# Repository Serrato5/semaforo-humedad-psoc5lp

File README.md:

# Semáforo de humedad del suelo para PSoC 5LP

Tarjeta de expansión para la **PSoC 5LP (CY8CKIT-059)** que clasifica la humedad del suelo en **seco, semihúmedo o húmedo** con un semáforo de LED. La decisión es **100 % analógica**: un seguidor de voltaje, dos comparadores y una compuerta NOR internos de la PSoC comparan la señal de un sensor capacitivo con dos umbrales que se ajustan con trimmers. La CPU solo arranca los bloques y reporta el estado por USB.

Proyecto del curso **Electrónica Análoga 3**, Universidad Surcolombiana (Neiva), 2026-B. Docente: Ing. Julián Adolfo Ramírez Gutiérrez.

**[Bitácora del equipo (PDF)](documentos/Bitacora_del_equipo_Grupo4.pdf)** · **[Guía de estudio (PDF)](documentos/Guia_de_estudio_del_proyecto.pdf)** · **[Bitácora del proyecto](https://serrato5.github.io/semaforo-humedad-psoc5lp/bitacora.html)**: el recorrido completo, con los errores y las decisiones · **[Portafolio de Sebastián](https://serrato5.github.io/semaforo-humedad-psoc5lp/)** · **[Video del funcionamiento](https://youtu.be/htcd85bEVA8)**

## Equipo

| Integrante |
|---|
| Sebastián Serrato Ramírez · [LinkedIn](https://www.linkedin.com/in/sebaserrato) · [GitHub](https://github.com/Serrato5) |
| Juan Esteban Velásquez Perdomo |
| Keren Jireth Ramírez Rivera |
| Juan Diego Morales Parra |
| Juan Diego Valderrama Rodríguez |

## Resultados

| Prueba | Resultado |
|---|---|
| Suelo seco (Vbuf) | 2,68 V → LED rojo |
| Suelo húmedo (Vbuf) | 2,09 V → LED verde |
| Efecto de carga del multímetro en la salida del sensor | 2,68 V → 2,50 V (justifica el seguidor) |
| Protección con 12 V en el cable (simulación) | 5,64 V con 1N4007 · 5,19 V con Schottky B5819W |
| PCB por CNC (P4) | Separación mínima 0,84 mm (regla 0,6 mm) |
| PCB industrial (P5) | ERC 0 · DRC 0 · paridad esquemático–PCB 0 |
| Cotización JLCPCB (2 tarjetas ensambladas) | USD 19,03 + conectores USD 0,72 = **USD 19,75** (límite USD 20) |

## Cómo evolucionó

0. **Exploración (P1)**: generador de señales con WaveDAC8 (f = fs/N, error 0,4–2,2 %); de ahí salió la lección del efecto de carga del DAC que llevó al seguidor.
1. **ADC y software**: descartado, porque el curso exigía procesamiento analógico.
2. **Bloques analógicos con umbrales fijos en VDAC (firmware v1)**: había que reprogramar para cambiar un rango.
3. **Trimmers en la tarjeta (firmware v2)**: los rangos se ajustan sin computador, como pidió el usuario entrevistado.
4. **PCB de una cara fresada en CNC (P4)**.
5. **Tarjeta SMD de dos capas para ensamble en JLCPCB (P5)**, con socket parcial para enchufar la PSoC sin soldarla.

## Contenido del repositorio

```
firmware/
  v1_vdac/main.c          umbrales fijos con dos VDAC8
  v2_trimmers/main.c      versión final: umbrales por trimmer (P3[2], P3[3])
hardware/
  p4_pcb_cnc/             PCB de una cara: G-code para Mach3, Gerber, Excellon, KiCad y scripts
  p5_pcba/
    kicad/                proyecto KiCad 10 (esquemático, PCB, reportes ERC/DRC)
    fabricacion/          Gerber (zip), BOM y CPL en formato JLCPCB
    scripts/              generación del esquemático y la PCB, autorruteo y archivos de fabricación
    esquematico_P5.pdf
simulacion/               simulación en Python del semáforo y de la protección de entrada
documentos/               bitácora del equipo (PDF), guía de estudio, informe del P1 (WaveDAC8), expedientes técnicos del P4 y del P5, y el póster (80 × 160 cm)
docs/                     bitácora publicada con GitHub Pages
```

### Conexiones con la PSoC

| Señal | Pin del kit |
|---|---|
| Sensor protegido (SENS) | P3[0] |
| Salida del seguidor (Vbuf) | P3[1] |
| Umbral seco / húmedo | P3[2] / P3[3] |
| LED rojo / amarillo / verde | P2[3] / P2[4] / P2[5] |
| UART al PC (115200 baudios) | P12[7] |

### Regenerar la PCB del P5

Los scripts de `hardware/p5_pcba/scripts` usan KiCad 10 (`kicad-cli` y el módulo `pcbnew`) y Freerouting 2.5:

```sh
ROW=20.32 FLIP=0 sh build.sh   # esquemático, ERC, PCB, autorruteo, planos de GND y DRC
sh fab.sh                      # Gerber, taladros, BOM y CPL para JLCPCB
```

`ROW` es la distancia entre las filas J1 y J2 del kit. El valor de 20,32 mm (8 pasos de 2,54 mm) se verificó por fotogrametría: 51 agujeros detectados en una foto cenital del kit dan 8,0 ± 0,1 pasos entre filas. Conviene confirmarlo con calibrador antes de una compra real.

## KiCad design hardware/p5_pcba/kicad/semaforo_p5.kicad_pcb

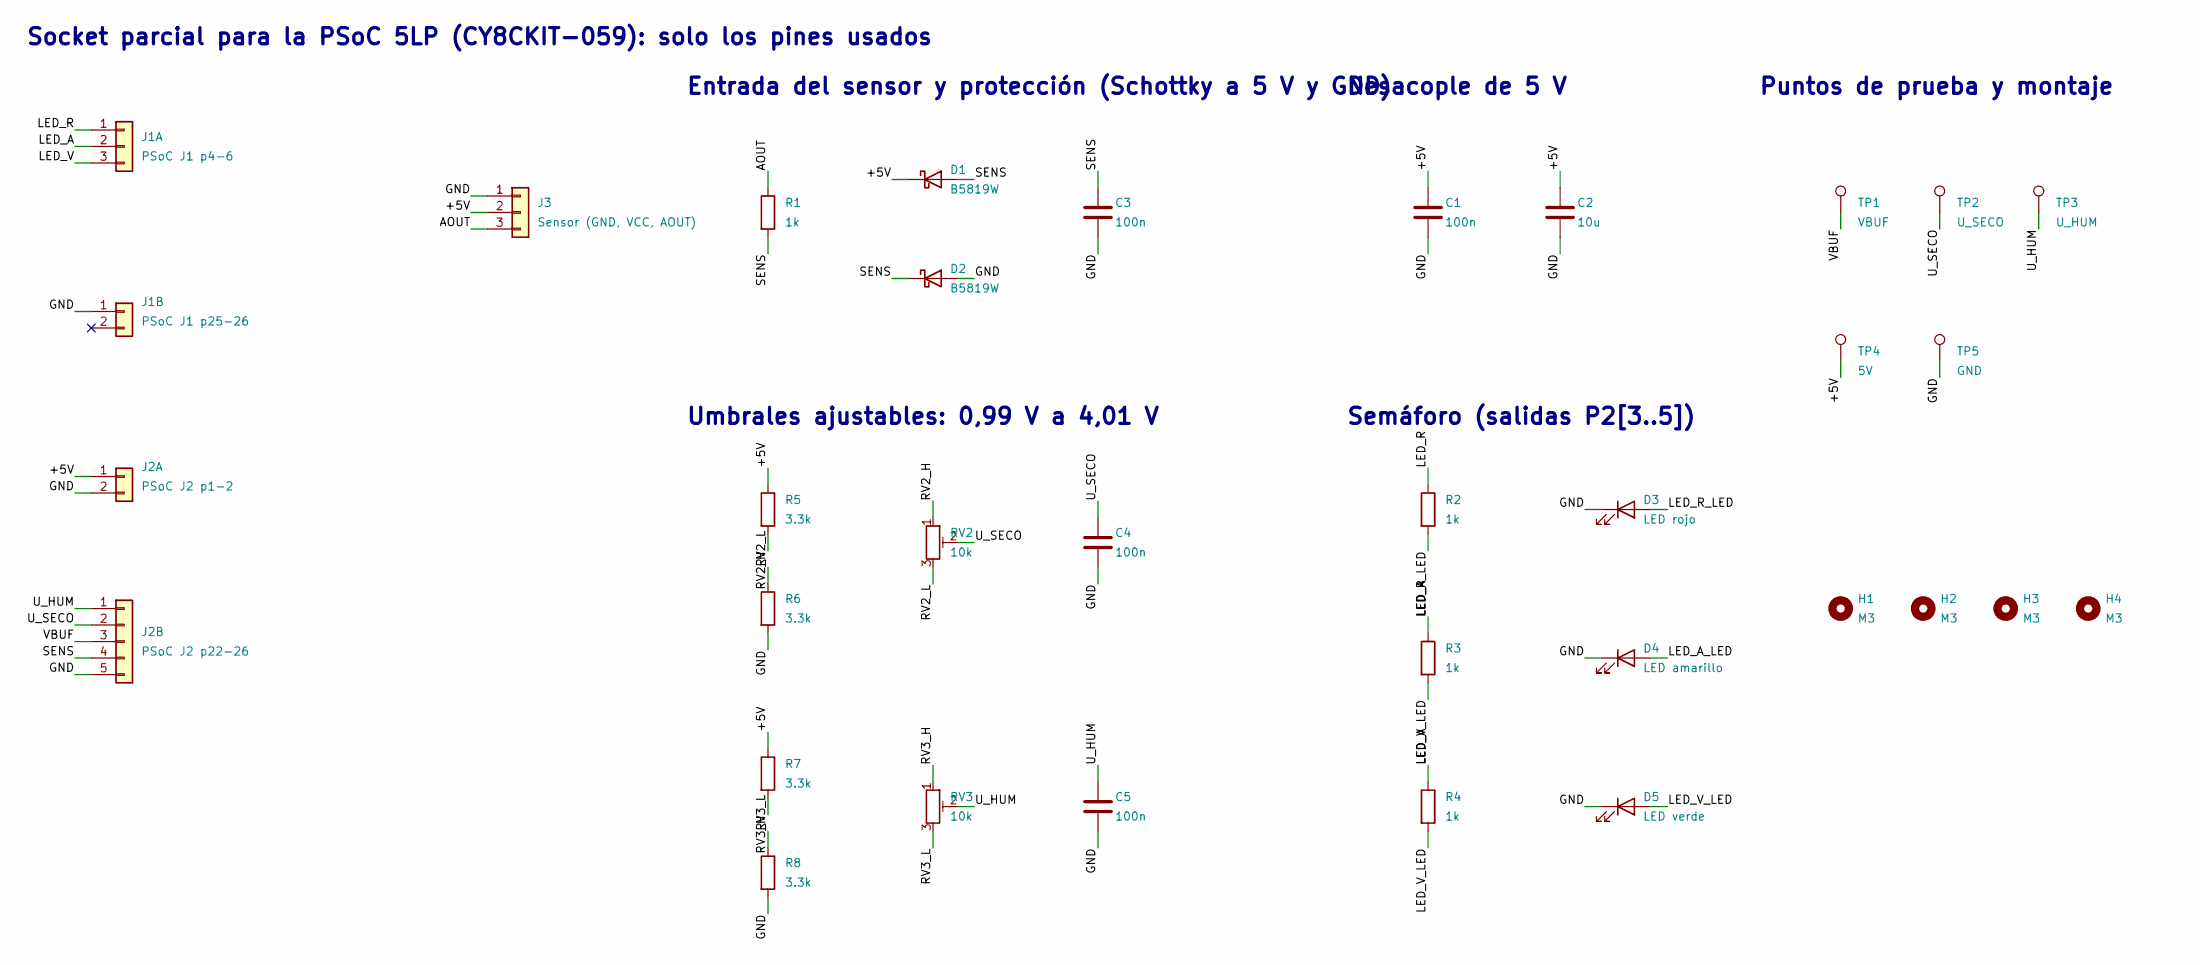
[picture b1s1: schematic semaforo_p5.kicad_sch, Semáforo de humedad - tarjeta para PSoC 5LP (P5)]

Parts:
C1, C3, C4, C5: 100n; C_0805_2012Metric; LCSC C49678
C2: 10u; C_0805_2012Metric; LCSC C15850
D1, D2: B5819W; D_SOD-123; LCSC C8598
D3: LED rojo; LED_0805_2012Metric; LCSC C84256
D4: LED amarillo; LED_0805_2012Metric; LCSC C2296
D5: LED verde; LED_0805_2012Metric; LCSC C2297
H1, H2, H3, H4: M3; MountingHole_3.2mm_M3
J1A: PSoC J1 p4-6; PinSocket_1x03_P2.54mm_Vertical
J1B: PSoC J1 p25-26; PinSocket_1x02_P2.54mm_Vertical
J2A: PSoC J2 p1-2; PinSocket_1x02_P2.54mm_Vertical
J2B: PSoC J2 p22-26; PinSocket_1x05_P2.54mm_Vertical
J3: Sensor (GND, VCC, AOUT); PinHeader_1x03_P2.54mm_Vertical
R1, R2, R3, R4: 1k; R_0805_2012Metric; LCSC C17513
R5, R6, R7, R8: 3.3k; R_0805_2012Metric; LCSC C26010
RV2, RV3: 10k; Potentiometer_Bourns_TC33X_Vertical; LCSC C719176
TP1: VBUF; TestPoint_Pad_D1.5mm
TP2: U_SECO; TestPoint_Pad_D1.5mm
TP3: U_HUM; TestPoint_Pad_D1.5mm
TP4: 5V; TestPoint_Pad_D1.5mm
TP5: GND; TestPoint_Pad_D1.5mm

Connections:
/+5V: C1.1, C2.1, D1.1 (K), J2A.1, J3.2, R5.1, R7.1, TP4.1
/AOUT: J3.3, R1.1
/GND: C1.2, C2.2, C3.2, C4.2, C5.2, D2.2 (A), D3.1 (K), D4.1 (K), D5.1 (K), J1B.1, J2A.2, J2B.5, J3.1, R6.2, R8.2, TP5.1
/LED_A: J1A.2, R3.1
/LED_A_LED: D4.2 (A), R3.2
/LED_R: J1A.1, R2.1
/LED_R_LED: D3.2 (A), R2.2
/LED_V: J1A.3, R4.1
/LED_V_LED: D5.2 (A), R4.2
/RV2_H: R5.2, RV2.1
/RV2_L: R6.1, RV2.3
/RV3_H: R7.2, RV3.1
/RV3_L: R8.1, RV3.3
/SENS: C3.1, D1.2 (A), D2.1 (K), J2B.4, R1.2
/U_HUM: C5.1, J2B.1, RV3.2, TP3.1
/U_SECO: C4.1, J2B.2, RV2.2, TP2.1
/VBUF: J2B.3, TP1.1

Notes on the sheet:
Socket parcial para la PSoC 5LP (CY8CKIT-059): solo los pines usados
Entrada del sensor y protección (Schottky a 5 V y GND)
Umbrales ajustables: 0,99 V a 4,01 V
Semáforo (salidas P2[3..5])
Desacople de 5 V
Puntos de prueba y montaje

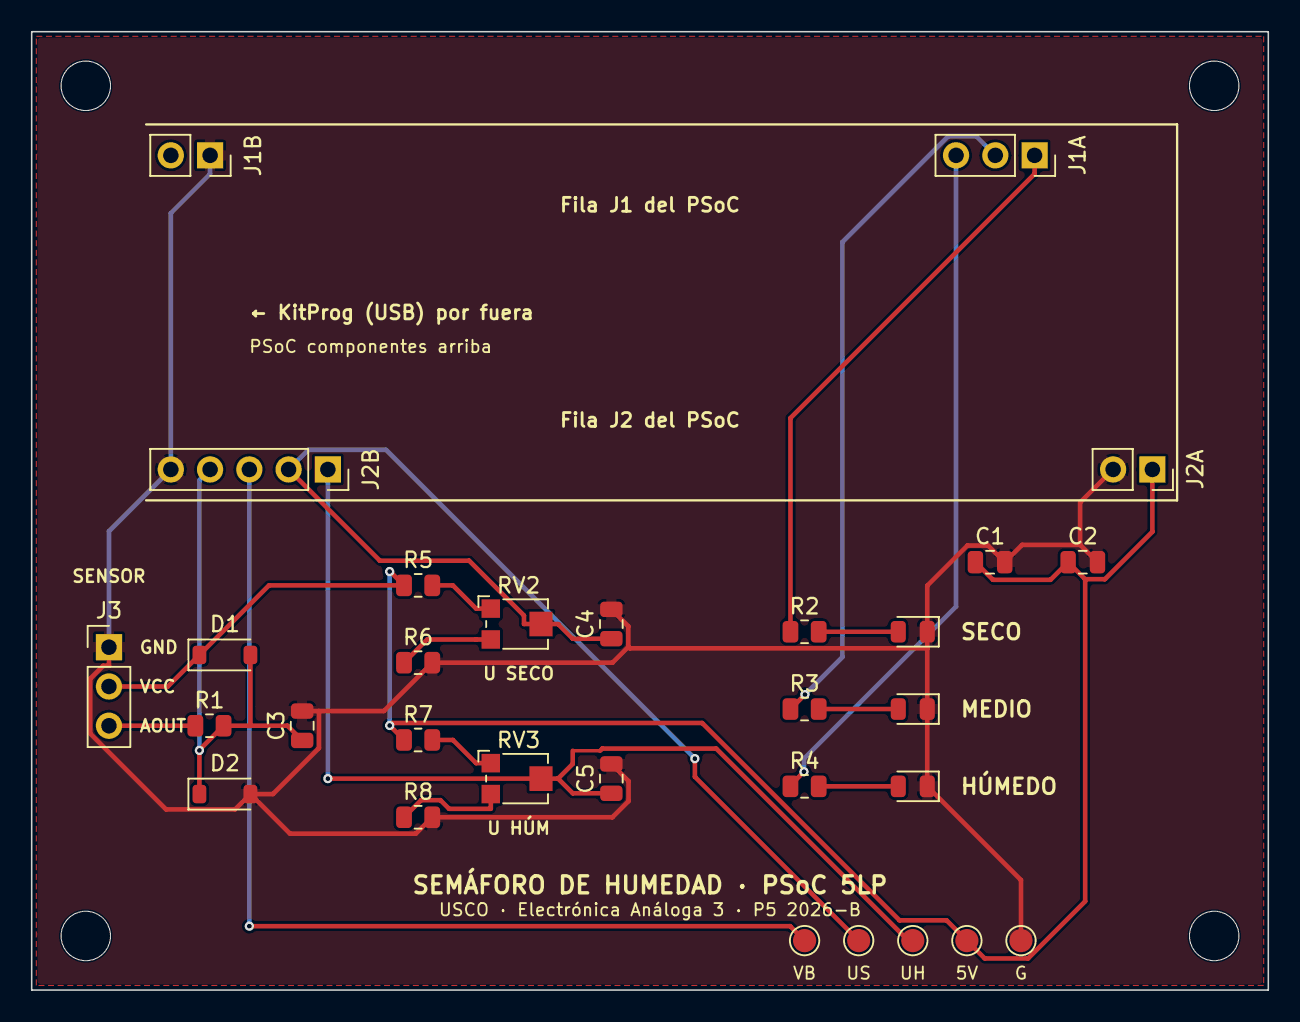
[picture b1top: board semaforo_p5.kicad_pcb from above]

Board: 2 copper layers, 80.0 x 62.0 mm, 34 parts (0 on the bottom side), 17 nets.

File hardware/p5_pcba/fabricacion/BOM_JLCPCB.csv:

Comment,Designator,Footprint,LCSC Part #
1k,"R1,R2,R3,R4",R_0805_2012Metric,C17513
B5819W,"D1,D2",D_SOD-123,C8598
100n,"C1,C3,C4,C5",C_0805_2012Metric,C49678
3.3k,"R5,R6,R7,R8",R_0805_2012Metric,C26010
10k,"RV2,RV3",Potentiometer_Bourns_TC33X_Vertical,C719176
LED rojo,D3,LED_0805_2012Metric,C84256
LED amarillo,D4,LED_0805_2012Metric,C2296
LED verde,D5,LED_0805_2012Metric,C2297
10u,C2,C_0805_2012Metric,C15850

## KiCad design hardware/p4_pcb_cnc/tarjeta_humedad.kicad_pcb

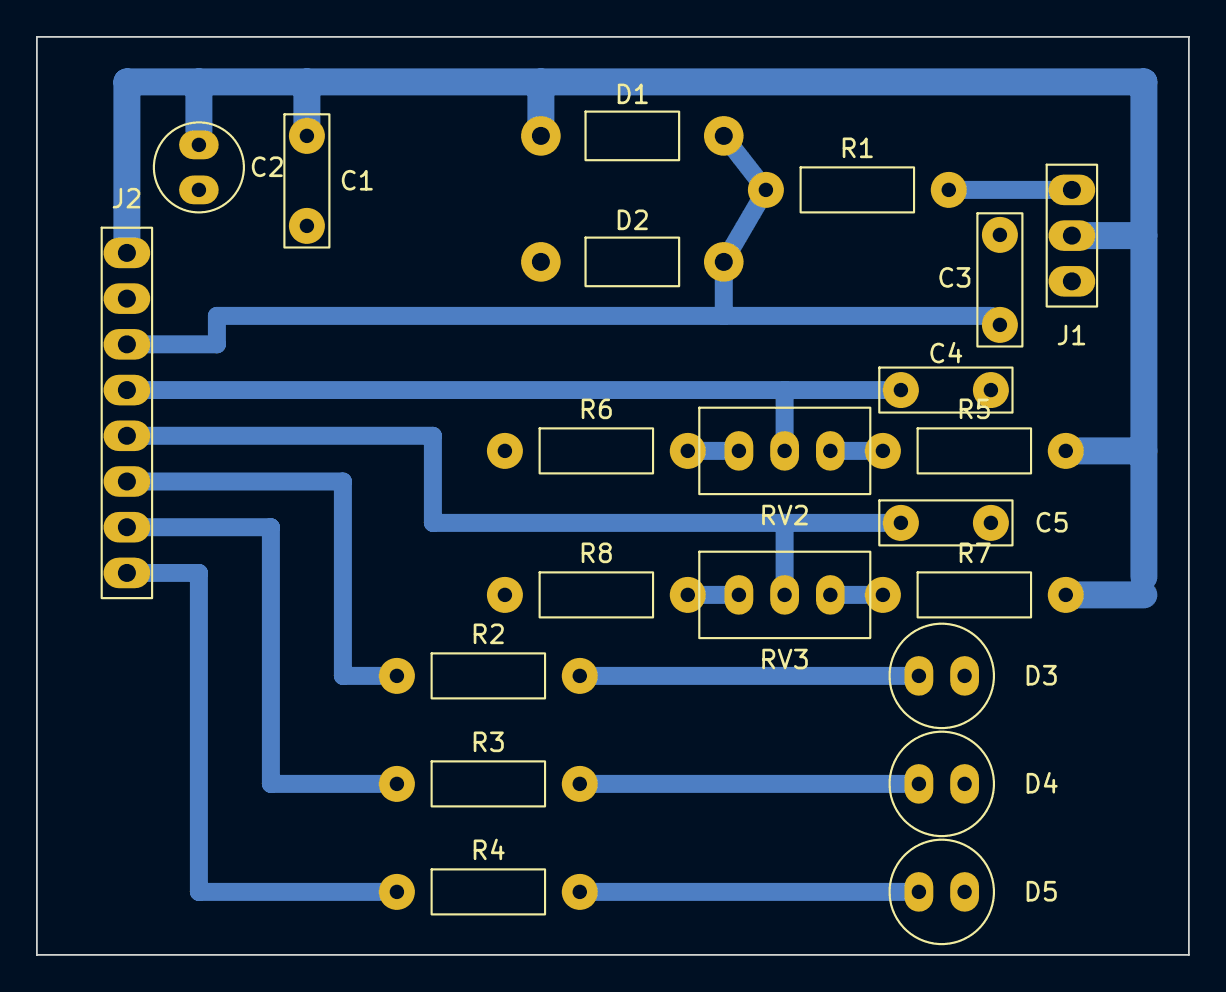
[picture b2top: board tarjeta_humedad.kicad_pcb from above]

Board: 2 copper layers, 64.0 x 51.0 mm, 22 parts (0 on the bottom side), 16 nets.

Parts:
C1, C3, C4, C5: 100n; C_Disc_D5.0mm_P5.00mm
C2: 10u; CP_Radial_D5.0mm_P2.50mm
D1, D2: 1N4007; D_DO-41_P10.16mm
D3: LED rojo; LED_D5.0mm
D4: LED amarillo; LED_D5.0mm
D5: LED verde; LED_D5.0mm
J1: Sensor; PinHeader_1x03_P2.54mm
J2: PSoC 1x8; PinHeader_1x08_P2.54mm
R1, R2, R3, R4: 1k; R_Axial_P10.16mm
R5, R6, R7, R8: 3k3; R_Axial_P10.16mm
RV2, RV3: 10k 3296W; Potentiometer_Bourns_3296W_Vertical

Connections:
+5V: C1.1, C2.1, D1.2, J1.2, J2.1, R5.2, R7.2
AOUT: J1.3, R1.2
GND: C1.2, C2.2, C3.2, C4.2, C5.2, D2.2, D3.1, D4.1, D5.1, J1.1, J2.2, R6.1, R8.1
LED_A: J2.7, R3.1
LED_A_K: D4.2, R3.2
LED_R: J2.6, R2.1
LED_R_K: D3.2, R2.2
LED_V: J2.8, R4.1
LED_V_K: D5.2, R4.2
N_RV2_A: R5.1, RV2.1
N_RV2_B: R6.2, RV2.3
N_RV3_A: R7.1, RV3.1
N_RV3_B: R8.2, RV3.3
SENS: C3.1, D1.1, D2.1, J2.3, R1.1
U_HUM: C5.1, J2.5, RV3.2
U_SECO: C4.1, J2.4, RV2.2
